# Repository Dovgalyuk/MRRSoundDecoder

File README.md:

# Maple RailRoad Sound Decoder

WiFi controller, sound decoder, and sound projects for model trains.

Project includes library for programming the sounds with set of state machines.

There are several ready-to-use sample sound projects.

# Project structure

* esp32 - firmwares for decoder and command station
* hardware - several versions of PCBs for manufacturing the decoder
* projects - ready-to-use sound projects for different locomotives
* compiler - compiler for the sound projects
* emulator - cab emulator for listening sounds with virtual locomotive control
* sample - dummy player which generates wav file by interpreting the sound project
* other directories include the source code of the firmware

# Bringing locomotive to life

* Get the hardware (order PCB, solder the components)
* Build firmware
  * Install ESP32 toolkit (esp idf)
  * Run esp32/decoder/build32M.sh (or other version)
* Upload esp32/decoder/build32M/esp32sounddecoder.bin into the ESP32 module
* Build selected sound project with compiler/compiler.py
* Upload built project through the web interface into the controller
* Install the controller into the locomotive

# Software features

Controller provides web interface that may be accessed through
WiFi (default address 192.168.4.1).

Sound module plays 8- or 16-bit sounds in 8 channels.

Output functions and sound schemes are programmed with
custom language. The scripts may include conditions,
loops, and finite state machines. These features
may be used for creating complex sound projects.

# Hardware

Controller is intended to be used with G-scale locomotives
with lithium batteries installed, but it may also be used
with track power (some power capacitors are probably needed).

Controller includes the following hardware components:
* ESP32 CPU with embedded WiFi module and flash memory
* Motor driver
* I2S audio power amplifier (MAX98357A)
* 7 programmable outputs
* BEMF for adjusting the motor speed (work in progress)

# Roadmap

* BEMF with new motor driver
* Support of logical input/outputs
* H0-compatible PCB

# Links

* Radio-controlled engines with sound
  - https://github.com/TheDIYGuy999/Rc_Engine_Sound_ESP32
* Cost effective DIY DCC Decoder for model railroad locomotives
  - https://github.com/gab-k/RP2040-Decoder
* NIMRS: open-source NIMRS-21Pin-Decoder, based on the ESP32-S3 microcontroller
  - https://github.com/CDFER/NIMRS-21Pin-Decoder
  - https://github.com/ProjectInitiative/NIMRS-Firmware

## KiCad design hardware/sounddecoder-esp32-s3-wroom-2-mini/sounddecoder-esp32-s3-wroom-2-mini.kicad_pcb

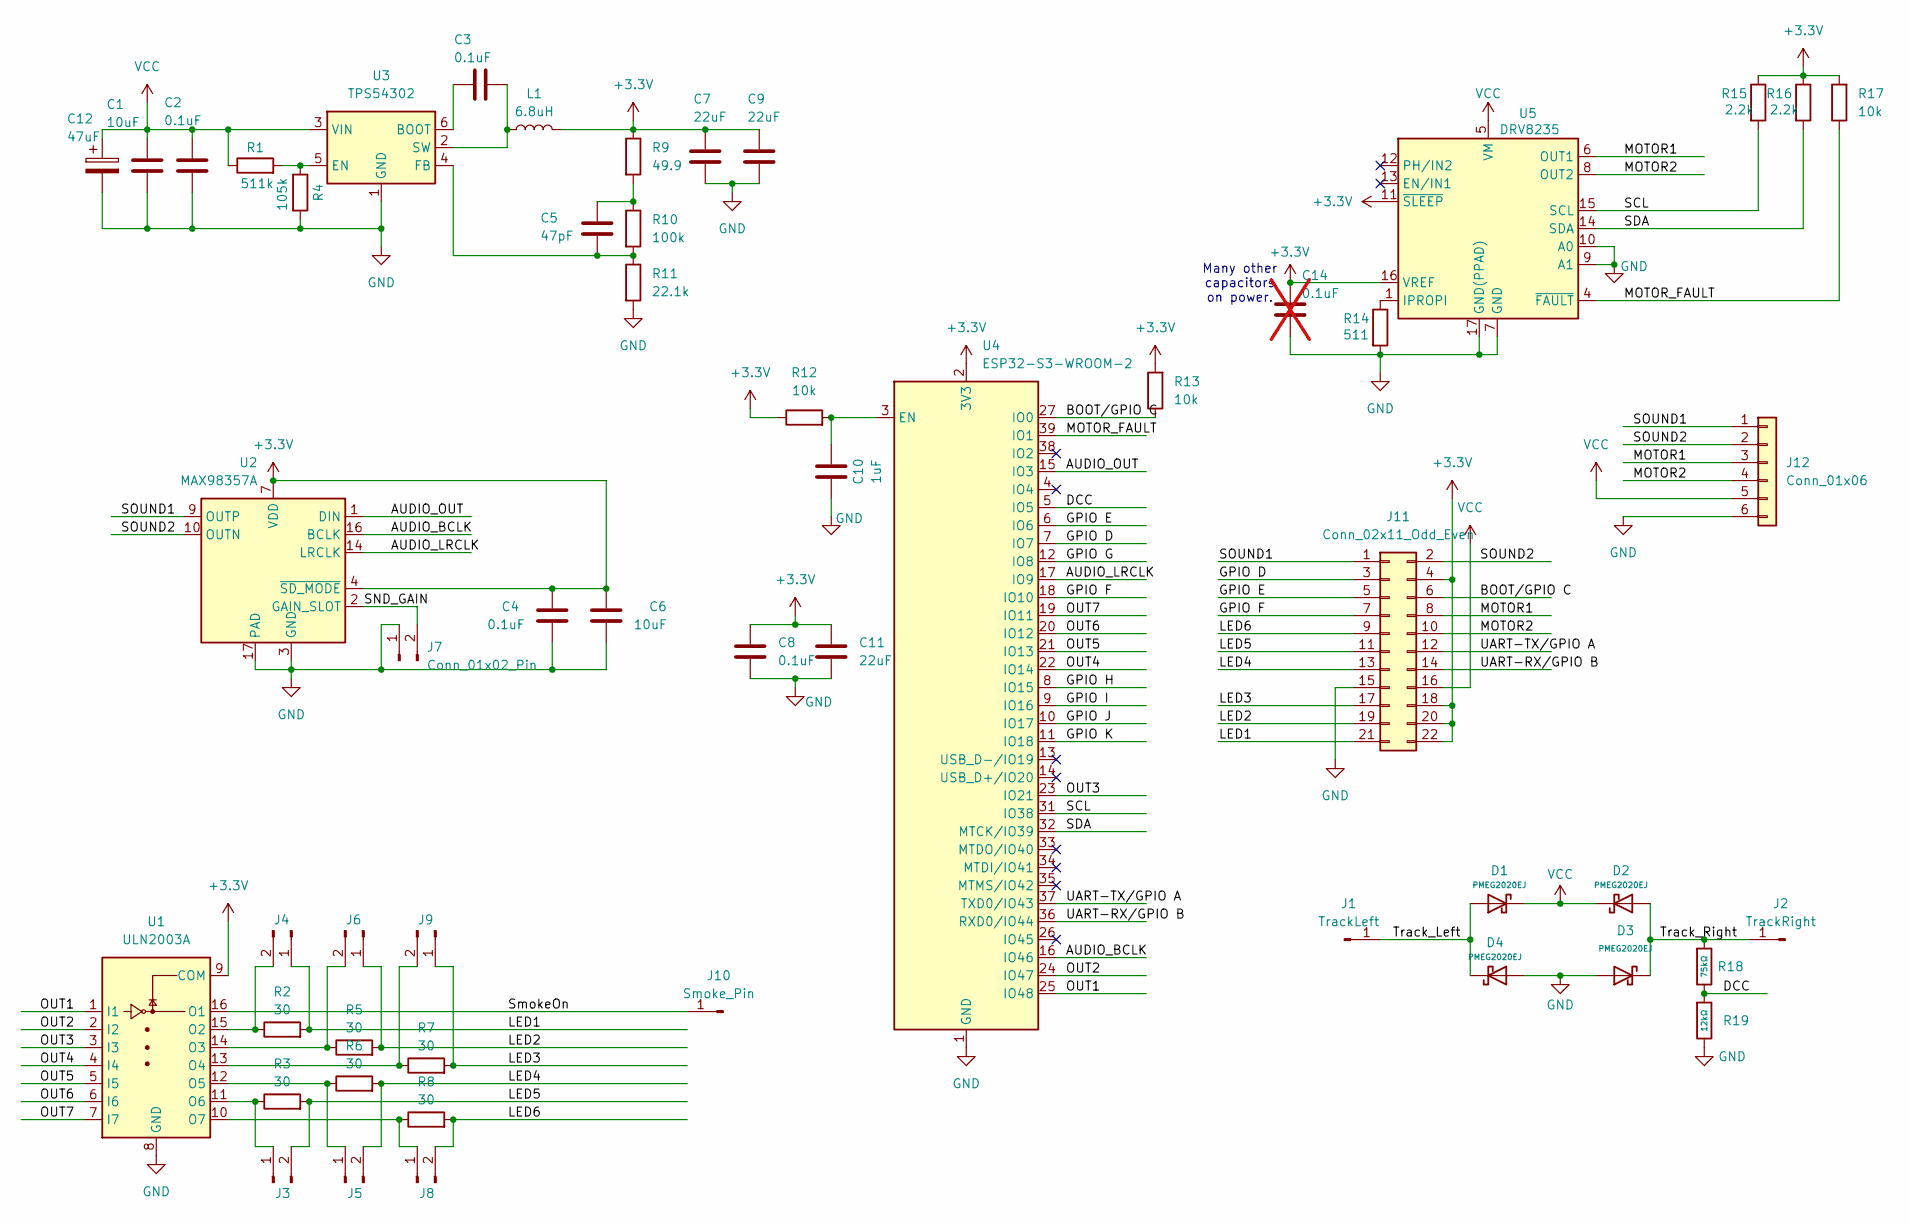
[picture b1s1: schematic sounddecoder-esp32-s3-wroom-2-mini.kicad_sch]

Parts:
C1, C6: 10uF; C_0603_1608Metric
C2, C3, C4, C8: 0.1uF; C_0603_1608Metric
C5: 47pF; C_0603_1608Metric
C7, C9, C11: 22uF; C_0603_1608Metric
C10: 1uF; C_0603_1608Metric
C12: 47uF; CP_Elec_6.3x5.4
C14: 0.1uF; C_0603_1608Metric; not fitted
D1, D2, D3, D4: PMEG2020EJ; D_SOD-323; Forward Voltage (Vf@If) 450mV@1.0A; Reverse Voltage (Vr) 20V; Part B5817WS; LCSC C7420329
J1: TrackLeft; TestPoint_THTPad_1.0x1.0mm_Drill0.5mm
J2: TrackRight; TestPoint_THTPad_1.0x1.0mm_Drill0.5mm
J3, J4, J5, J6, J7, J8, J9: Conn_01x02_Pin; SolderJumper-2_P1.3mm_Open_RoundedPad1.0x1.5mm
J10: Smoke_Pin; TestPoint_THTPad_1.0x1.0mm_Drill0.5mm
J11: Conn_02x11_Odd_Even; PinHeader_2x11_P2.00mm_Vertical
J12: Conn_01x06; PinHeader_1x06_P2.54mm_Vertical
L1: 6.8uH; L_Chilisin_BMRA00050530
R1: 511k; C_0603_1608Metric
R2, R3, R5, R6, R7, R8: 30; C_0603_1608Metric
R4: 105k; C_0603_1608Metric
R9: 49.9; C_0603_1608Metric
R10: 100k; C_0603_1608Metric
R11: 22.1k; C_0603_1608Metric
R12, R13, R17: 10k; C_0603_1608Metric
R14: 511; C_0603_1608Metric
R15, R16: 2.2k; C_0603_1608Metric
R18: 75kΩ; C_0603_1608Metric; Overload Voltage (Max) 50V; Tolerance ±1%; Part 0402WGF7502TCE; LCSC C25798
R19: 12kΩ; C_0603_1608Metric; Overload Voltage (Max) 50V; Tolerance ±1%; Part 0402WGF2002TCE; LCSC C25765
U1: ULN2003A; SO-16_3.9x9.9mm_P1.27mm
U2: MAX98357A; TQFN-16-1EP_3x3mm_P0.5mm_EP1.23x1.23mm
U3: TPS54302; SOT-23-6
U4: ESP32-S3-WROOM-2
U5: DRV8235; WQFN-16-1EP_3x3mm_P0.5mm_EP1.68x1.68mm_ThermalVias

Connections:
+3.3V: C4.1, C6.1, C7.1, C8.1, C9.1, C11.1, C14.1, J11.4, J11.18, J11.20, J11.22, L1.2, R9.1, R12.1, R13.2, R15.1, R16.1, R17.2, U1.9 (COM), U2.4 (~SD_MODE), U2.7 (VDD), U2.8 (VDD), U4.2 (3V3), U5.11 (~SLEEP), U5.16 (VREF)
/AUDIO_BCLK: U2.16 (BCLK), U4.16 (IO46)
/AUDIO_LRCLK: U2.14 (LRCLK), U4.17 (IO9)
/AUDIO_OUT: U2.1 (DIN), U4.15 (IO3)
/BOOT/GPIO C: J11.6, R13.1, U4.27 (IO0)
/DCC: R18.2, R19.1, U4.5 (IO5)
/GPIO D: J11.3, U4.7 (IO7)
/GPIO E: J11.5, U4.6 (IO6)
/GPIO F: J11.7, U4.18 (IO10)
/GPIO G: U4.12 (IO8)
/GPIO H: U4.8 (IO15)
/GPIO I: U4.9 (IO16)
/GPIO J: U4.10 (IO17)
/GPIO K: U4.11 (IO18)
/LED1: J4.1, J11.21, R2.2
/LED2: J6.1, J11.19, R5.2
/LED3: J9.1, J11.17, R7.2
/LED4: J5.2, J11.13, R6.2
/LED5: J3.2, J11.11, R3.2
/LED6: J8.2, J11.9, R8.2
/MOTOR1: J11.8, J12.3, U5.6 (OUT1)
/MOTOR2: J11.10, J12.4, U5.8 (OUT2)
/MOTOR_FAULT: R17.1, U4.39 (IO1), U5.4 (~FAULT)
/OUT1: U1.1 (I1), U4.25 (IO48)
/OUT2: U1.2 (I2), U4.24 (IO47)
/OUT3: U1.3 (I3), U4.23 (IO21)
/OUT4: U1.4 (I4), U4.22 (IO14)
/OUT5: U1.5 (I5), U4.21 (IO13)
/OUT6: U1.6 (I6), U4.20 (IO12)
/OUT7: U1.7 (I7), U4.19 (IO11)
/SCL: R15.2, U4.31 (IO38), U5.15 (SCL)
/SDA: R16.2, U4.32 (MTCK/IO39), U5.14 (SDA)
/SND_GAIN: J7.2, U2.2 (GAIN_SLOT)
/SOUND1: J11.1, J12.1, U2.9 (OUTP)
/SOUND2: J11.2, J12.2, U2.10 (OUTN)
/SmokeOn: J10.1, U1.16 (O1)
/Track_Left: D1.2, D4.1, J1.1
/Track_Right: D2.2, D3.1, J2.1, R18.1
/UART-RX/GPIO B: J11.14, U4.36 (RXD0/IO44)
/UART-TX/GPIO A: J11.12, U4.37 (TXD0/IO43)
GND: C1.2, C2.2, C4.2, C6.2, C7.2, C8.2, C9.2, C10.1, C11.2, C12.2, C14.2, D3.2, D4.2, J7.1, J11.15, J12.6, R4.2, R11.2, R14.2, R19.2, U1.8 (GND), U2.3 (GND), U2.11 (GND), U2.15 (GND), U2.17 (PAD), U3.1 (GND), U4.1 (GND), U4.40 (GND), U4.41 (GND), U5.7 (GND), U5.9 (A1), U5.10 (A0), U5.17 (GND(PPAD))
unnamed: C5.1, R9.2, R10.1
unnamed: J3.1, R3.1, U1.11 (O6)
unnamed: J4.2, R2.1, U1.15 (O2)
unnamed: J5.1, R6.1, U1.12 (O5)
unnamed: J6.2, R5.1, U1.14 (O3)
unnamed: J8.1, R8.1, U1.10 (O7)
unnamed: J9.2, R7.1, U1.13 (O4)
unnamed: C3.1, U3.6 (BOOT)
unnamed: R1.2, R4.1, U3.5 (EN)
unnamed: C5.2, R10.2, R11.1, U3.4 (FB)
unnamed: C3.2, L1.1, U3.2 (SW)
unnamed: C10.2, R12.2, U4.3 (EN)
unnamed: R14.1, U5.1 (IPROPI)
VCC: C1.1, C2.1, C12.1, D1.1, D2.1, J11.16, J12.5, R1.1, U3.3 (VIN), U5.5 (VM)

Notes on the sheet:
Many other capacitors on power.

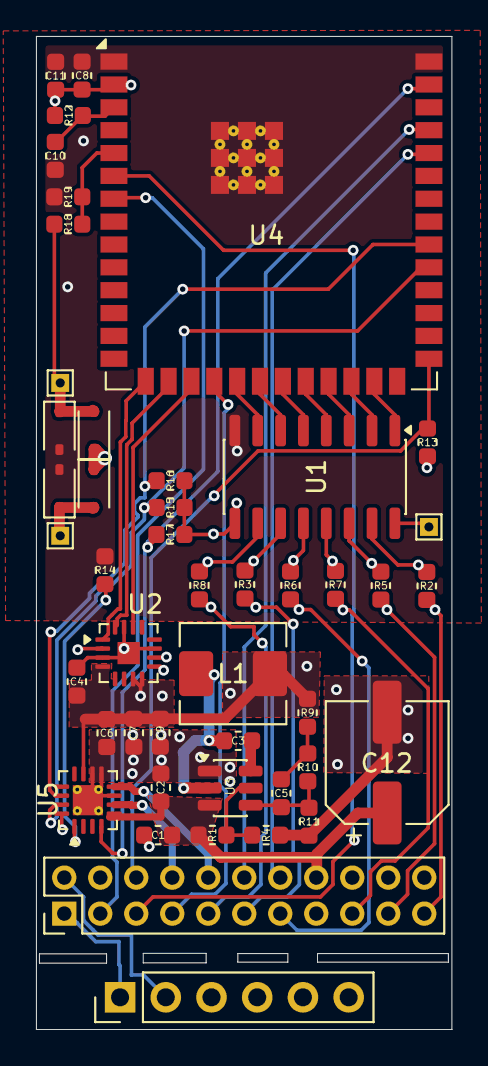
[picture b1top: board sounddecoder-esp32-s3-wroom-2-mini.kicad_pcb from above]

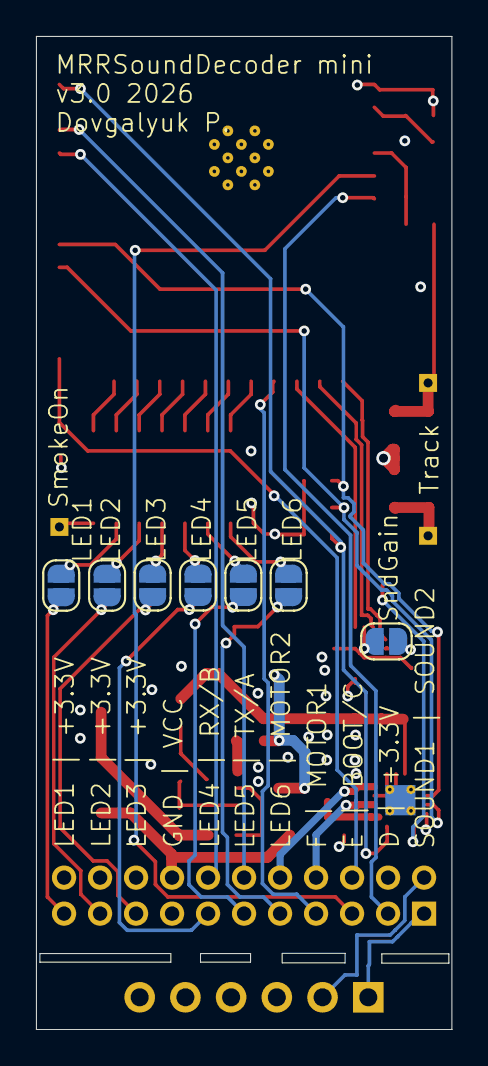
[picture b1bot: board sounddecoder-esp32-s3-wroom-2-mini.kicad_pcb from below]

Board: 4 copper layers, 23.1 x 55.2 mm, 53 parts (7 on the bottom side), 50 nets.

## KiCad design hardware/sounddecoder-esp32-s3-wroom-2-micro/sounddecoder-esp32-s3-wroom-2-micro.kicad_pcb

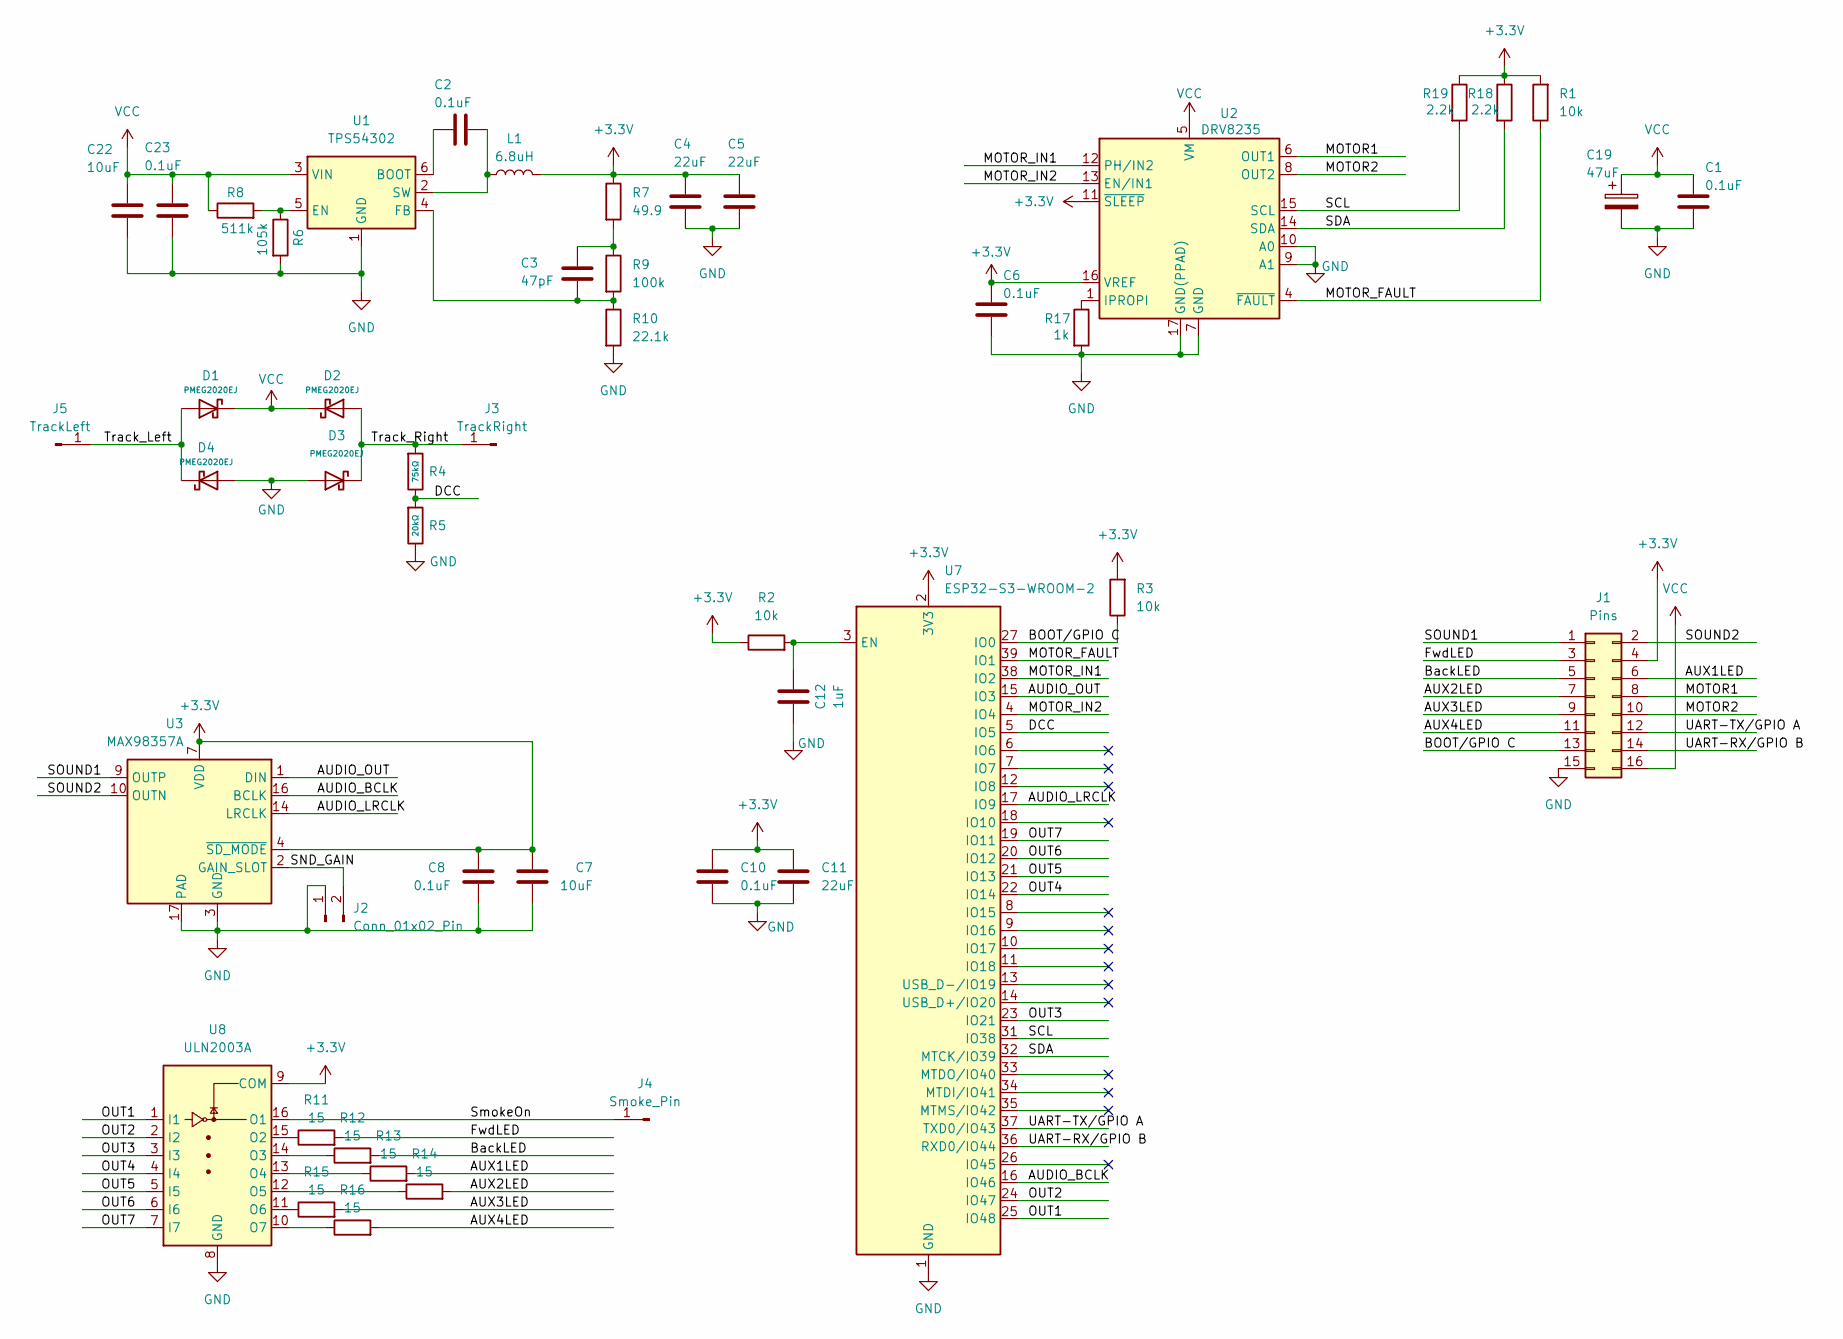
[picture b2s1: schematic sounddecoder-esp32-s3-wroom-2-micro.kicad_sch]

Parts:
C1, C2, C6, C8, C10, C23: 0.1uF; C_0603_1608Metric
C3: 47pF; C_0603_1608Metric
C4, C5, C11: 22uF; C_0603_1608Metric
C7, C22: 10uF; C_0603_1608Metric
C12: 1uF; C_0603_1608Metric
C19: 47uF; CP_Elec_6.3x5.4
D1, D2, D3, D4: PMEG2020EJ; D_SOD-323; Forward Voltage (Vf@If) 450mV@1.0A; Reverse Voltage (Vr) 20V; Part B5817WS; LCSC C7420329
J1: Pins; PinHeader_2x08_P2.00mm_Vertical
J2: Conn_01x02_Pin; SolderJumper-2_P1.3mm_Open_RoundedPad1.0x1.5mm
J3: TrackRight; TestPoint_THTPad_1.0x1.0mm_Drill0.5mm
J4: Smoke_Pin; TestPoint_THTPad_1.0x1.0mm_Drill0.5mm
J5: TrackLeft; TestPoint_THTPad_1.0x1.0mm_Drill0.5mm
L1: 6.8uH; L_Chilisin_BMRA00050530
R1, R2, R3: 10k; C_0603_1608Metric
R4: 75kΩ; C_0603_1608Metric; Overload Voltage (Max) 50V; Tolerance ±1%; Part 0402WGF7502TCE; LCSC C25798
R5: 20kΩ; C_0603_1608Metric; Overload Voltage (Max) 50V; Tolerance ±1%; Part 0402WGF2002TCE; LCSC C25765
R6: 105k; C_0603_1608Metric
R7: 49.9; C_0603_1608Metric
R8: 511k; C_0603_1608Metric
R9: 100k; C_0603_1608Metric
R10: 22.1k; C_0603_1608Metric
R11, R12, R13, R14, R15, R16: 15; C_0603_1608Metric
R17: 1k; C_0603_1608Metric
R18, R19: 2.2k; C_0603_1608Metric
U1: TPS54302; SOT-23-6
U2: DRV8235; WQFN-16-1EP_3x3mm_P0.5mm_EP1.68x1.68mm_ThermalVias
U3: MAX98357A; TQFN-16-1EP_3x3mm_P0.5mm_EP1.23x1.23mm
U7: ESP32-S3-WROOM-2
U8: ULN2003A; SO-16_3.9x9.9mm_P1.27mm

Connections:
+3.3V: C4.1, C5.1, C6.1, C7.1, C8.1, C10.1, C11.1, J1.4, L1.2, R1.2, R2.1, R3.2, R7.1, R18.1, R19.1, U2.11 (~SLEEP), U2.16 (VREF), U3.4 (~SD_MODE), U3.7 (VDD), U3.8 (VDD), U7.2 (3V3), U8.9 (COM)
/AUDIO_BCLK: U3.16 (BCLK), U7.16 (IO46)
/AUDIO_LRCLK: U3.14 (LRCLK), U7.17 (IO9)
/AUDIO_OUT: U3.1 (DIN), U7.15 (IO3)
/AUX1LED: J1.6, R13.2
/AUX2LED: J1.7, R14.2
/AUX3LED: J1.9, R15.2
/AUX4LED: J1.11, R16.2
/BOOT/GPIO C: J1.13, R3.1, U7.27 (IO0)
/BackLED: J1.5, R12.2
/DCC: R4.2, R5.1, U7.5 (IO5)
/FwdLED: J1.3, R11.2
/MOTOR1: J1.8, U2.6 (OUT1)
/MOTOR2: J1.10, U2.8 (OUT2)
/MOTOR_FAULT: R1.1, U2.4 (~FAULT), U7.39 (IO1)
/MOTOR_IN1: U2.12 (PH/IN2), U7.38 (IO2)
/MOTOR_IN2: U2.13 (EN/IN1), U7.4 (IO4)
/OUT1: U7.25 (IO48), U8.1 (I1)
/OUT2: U7.24 (IO47), U8.2 (I2)
/OUT3: U7.23 (IO21), U8.3 (I3)
/OUT4: U7.22 (IO14), U8.4 (I4)
/OUT5: U7.21 (IO13), U8.5 (I5)
/OUT6: U7.20 (IO12), U8.6 (I6)
/OUT7: U7.19 (IO11), U8.7 (I7)
/SCL: R19.2, U2.15 (SCL), U7.31 (IO38)
/SDA: R18.2, U2.14 (SDA), U7.32 (MTCK/IO39)
/SND_GAIN: J2.2, U3.2 (GAIN_SLOT)
/SOUND1: J1.1, U3.9 (OUTP)
/SOUND2: J1.2, U3.10 (OUTN)
/SmokeOn: J4.1, U8.16 (O1)
/Track_Left: D1.2, D4.1, J5.1
/Track_Right: D2.2, D3.1, J3.1, R4.1
/UART-RX/GPIO B: J1.14, U7.36 (RXD0/IO44)
/UART-TX/GPIO A: J1.12, U7.37 (TXD0/IO43)
GND: C1.2, C4.2, C5.2, C6.2, C7.2, C8.2, C10.2, C11.2, C12.1, C19.2, C22.2, C23.2, D3.2, D4.2, J1.15, J2.1, R5.2, R6.2, R10.2, R17.2, U1.1 (GND), U2.7 (GND), U2.9 (A1), U2.10 (A0), U2.17 (GND(PPAD)), U3.3 (GND), U3.11 (GND), U3.15 (GND), U3.17 (PAD), U7.1 (GND), U7.40 (GND), U7.41 (GND), U8.8 (GND)
unnamed: C3.1, R7.2, R9.1
unnamed: C2.1, U1.6 (BOOT)
unnamed: R6.1, R8.2, U1.5 (EN)
unnamed: C3.2, R9.2, R10.1, U1.4 (FB)
unnamed: C2.2, L1.1, U1.2 (SW)
unnamed: R17.1, U2.1 (IPROPI)
unnamed: C12.2, R2.2, U7.3 (EN)
unnamed: R11.1, U8.15 (O2)
unnamed: R12.1, U8.14 (O3)
unnamed: R13.1, U8.13 (O4)
unnamed: R14.1, U8.12 (O5)
unnamed: R15.1, U8.11 (O6)
unnamed: R16.1, U8.10 (O7)
VCC: C1.1, C19.1, C22.1, C23.1, D1.1, D2.1, J1.16, R8.1, U1.3 (VIN), U2.5 (VM)

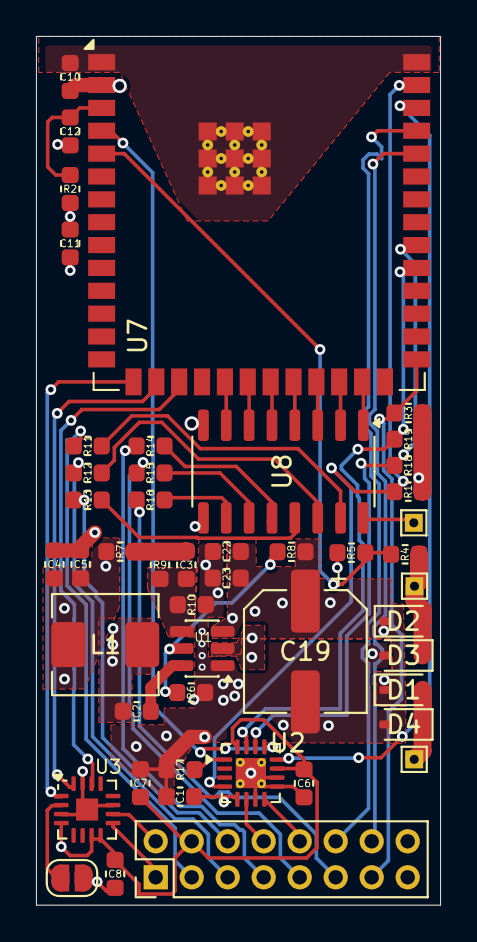
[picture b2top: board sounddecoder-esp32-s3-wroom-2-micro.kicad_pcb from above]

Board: 4 copper layers, 22.5 x 48.3 mm, 48 parts (0 on the bottom side), 49 nets.

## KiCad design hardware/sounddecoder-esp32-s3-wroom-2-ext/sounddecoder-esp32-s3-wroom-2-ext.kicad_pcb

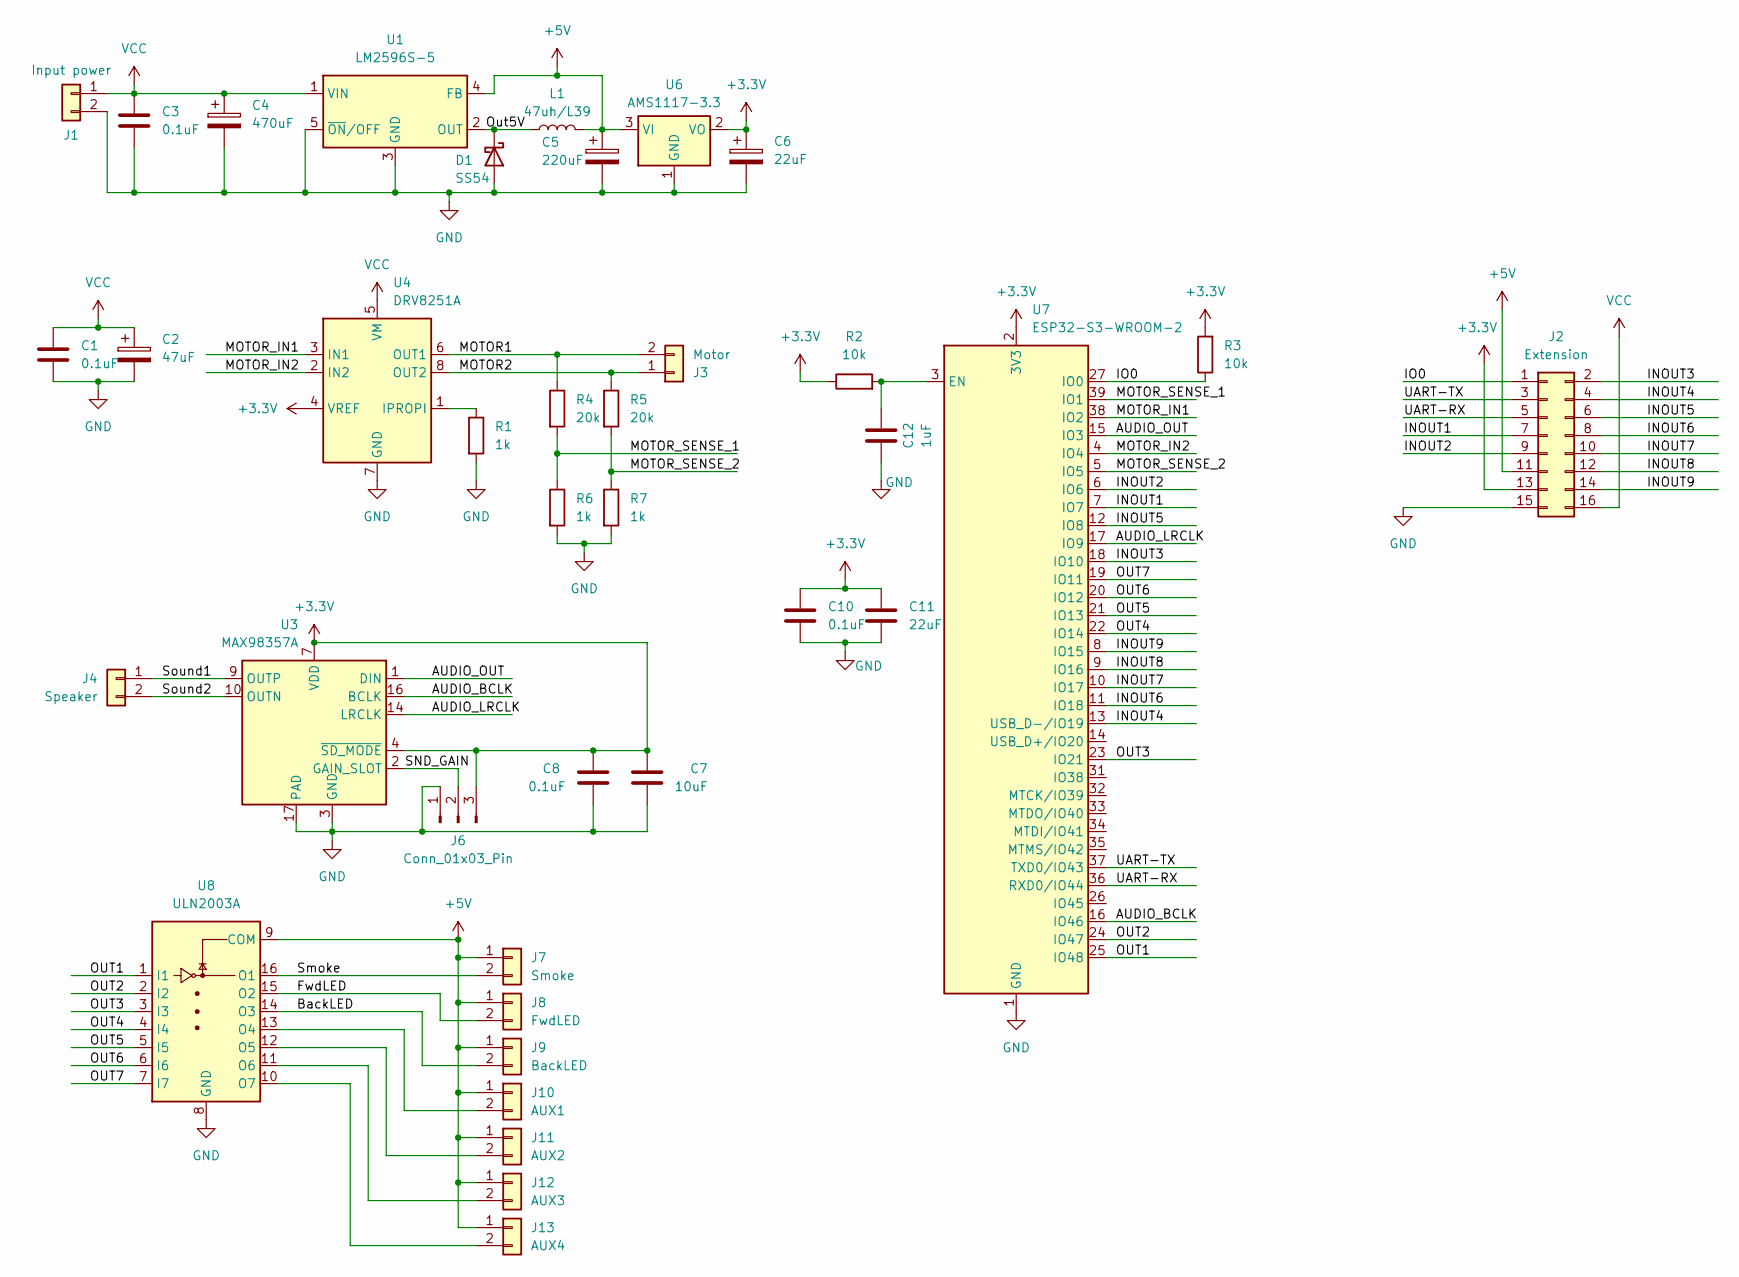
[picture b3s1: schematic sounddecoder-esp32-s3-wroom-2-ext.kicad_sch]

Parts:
C1, C3, C8, C10: 0.1uF; C_0805_2012Metric_Pad1.18x1.45mm_HandSolder
C2: 47uF; CP_Elec_6.3x5.4
C4: 470uF; CP_Elec_10x10.5
C5: 220uF; C_Elec_6.3x7.7
C6: 22uF; CP_Elec_4x5.4
C7: 10uF; C_0805_2012Metric_Pad1.18x1.45mm_HandSolder
C11: 22uF; C_0805_2012Metric_Pad1.18x1.45mm_HandSolder
C12: 1uF; C_0805_2012Metric_Pad1.18x1.45mm_HandSolder
D1: SS54; D_SMC
J1: Input power; TerminalBlock_Xinya_XY308-2.54-2P_1x02_P2.54mm_Horizontal
J2: Extension; PinHeader_2x08_P1.27mm_Vertical_SMD
J3: Motor; TerminalBlock_Xinya_XY308-2.54-2P_1x02_P2.54mm_Horizontal
J4: Speaker; TerminalBlock_Xinya_XY308-2.54-2P_1x02_P2.54mm_Horizontal
J6: Conn_01x03_Pin; PinHeader_1x03_P1.00mm_Vertical
J7: Smoke; TerminalBlock_Xinya_XY308-2.54-2P_1x02_P2.54mm_Horizontal
J8: FwdLED; TerminalBlock_Xinya_XY308-2.54-2P_1x02_P2.54mm_Horizontal
J9: BackLED; TerminalBlock_Xinya_XY308-2.54-2P_1x02_P2.54mm_Horizontal
J10: AUX1; TerminalBlock_Xinya_XY308-2.54-2P_1x02_P2.54mm_Horizontal
J11: AUX2; TerminalBlock_Xinya_XY308-2.54-2P_1x02_P2.54mm_Horizontal
J12: AUX3; TerminalBlock_Xinya_XY308-2.54-2P_1x02_P2.54mm_Horizontal
J13: AUX4; TerminalBlock_Xinya_XY308-2.54-2P_1x02_P2.54mm_Horizontal
L1: 47uh/L39; L_Bourns_SRP1245A
R1, R6, R7: 1k; R_0805_2012Metric_Pad1.20x1.40mm_HandSolder
R2, R3: 10k; R_0805_2012Metric_Pad1.20x1.40mm_HandSolder
R4, R5: 20k; R_0805_2012Metric_Pad1.20x1.40mm_HandSolder
U1: LM2596S-5; TO-263-5_TabPin3
U3: MAX98357A; TQFN-16-1EP_3x3mm_P0.5mm_EP1.23x1.23mm
U4: DRV8251A; Texas_HSOP-8-1EP_3.9x4.9mm_P1.27mm_ThermalVias
U6: AMS1117-3.3; SOT-223-3_TabPin2
U7: ESP32-S3-WROOM-2
U8: ULN2003A; SO-16_3.9x9.9mm_P1.27mm

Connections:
+3.3V: C6.1, C7.1, C8.1, C10.1, C11.1, J2.13, J6.3, R2.1, R3.2, U3.4 (~SD_MODE), U3.7 (VDD), U3.8 (VDD), U4.4 (VREF), U6.2 (VO), U7.2 (3V3)
+5V: C5.1, J2.11, J7.1, J8.1, J9.1, J10.1, J11.1, J12.1, J13.1, L1.2, U1.4 (FB), U6.3 (VI), U8.9 (COM)
/AUDIO_BCLK: U3.16 (BCLK), U7.16 (IO46)
/AUDIO_LRCLK: U3.14 (LRCLK), U7.17 (IO9)
/AUDIO_OUT: U3.1 (DIN), U7.15 (IO3)
/BackLED: J9.2, U8.14 (O3)
/FwdLED: J8.2, U8.15 (O2)
/INOUT1: J2.7, U7.7 (IO7)
/INOUT2: J2.9, U7.6 (IO6)
/INOUT3: J2.2, U7.18 (IO10)
/INOUT4: J2.4, U7.13 (USB_D-/IO19)
/INOUT5: J2.6, U7.12 (IO8)
/INOUT6: J2.8, U7.11 (IO18)
/INOUT7: J2.10, U7.10 (IO17)
/INOUT8: J2.12, U7.9 (IO16)
/INOUT9: J2.14, U7.8 (IO15)
/IO0: J2.1, R3.1, U7.27 (IO0)
/MOTOR1: J3.2, R4.1, U4.6 (OUT1)
/MOTOR2: J3.1, R5.1, U4.8 (OUT2)
/MOTOR_IN1: U4.3 (IN1), U7.38 (IO2)
/MOTOR_IN2: U4.2 (IN2), U7.4 (IO4)
/MOTOR_SENSE_1: R4.2, R6.1, U7.39 (IO1)
/MOTOR_SENSE_2: R5.2, R7.1, U7.5 (IO5)
/OUT1: U7.25 (IO48), U8.1 (I1)
/OUT2: U7.24 (IO47), U8.2 (I2)
/OUT3: U7.23 (IO21), U8.3 (I3)
/OUT4: U7.22 (IO14), U8.4 (I4)
/OUT5: U7.21 (IO13), U8.5 (I5)
/OUT6: U7.20 (IO12), U8.6 (I6)
/OUT7: U7.19 (IO11), U8.7 (I7)
/Out5V: D1.1 (K), L1.1, U1.2 (OUT)
/SND_GAIN: J6.2, U3.2 (GAIN_SLOT)
/Smoke: J7.2, U8.16 (O1)
/Sound1: J4.1, U3.9 (OUTP)
/Sound2: J4.2, U3.10 (OUTN)
/UART-RX: J2.5, U7.36 (RXD0/IO44)
/UART-TX: J2.3, U7.37 (TXD0/IO43)
GND: C1.2, C2.2, C3.2, C4.2, C5.2, C6.2, C7.2, C8.2, C10.2, C11.2, C12.1, D1.2 (A), J1.2, J2.15, J6.1, R1.2, R6.2, R7.2, U1.3 (GND), U1.5 (~ON/OFF), U3.3 (GND), U3.11 (GND), U3.15 (GND), U3.17 (PAD), U4.7 (GND), U4.9 (GND), U6.1 (GND), U7.1 (GND), U7.40 (GND), U7.41 (GND), U8.8 (GND)
unnamed: J10.2, U8.13 (O4)
unnamed: J11.2, U8.12 (O5)
unnamed: J12.2, U8.11 (O6)
unnamed: J13.2, U8.10 (O7)
unnamed: R1.1, U4.1 (IPROPI)
unnamed: C12.2, R2.2, U7.3 (EN)
VCC: C1.1, C2.1, C3.1, C4.1, J1.1, J2.16, U1.1 (VIN), U4.5 (VM)

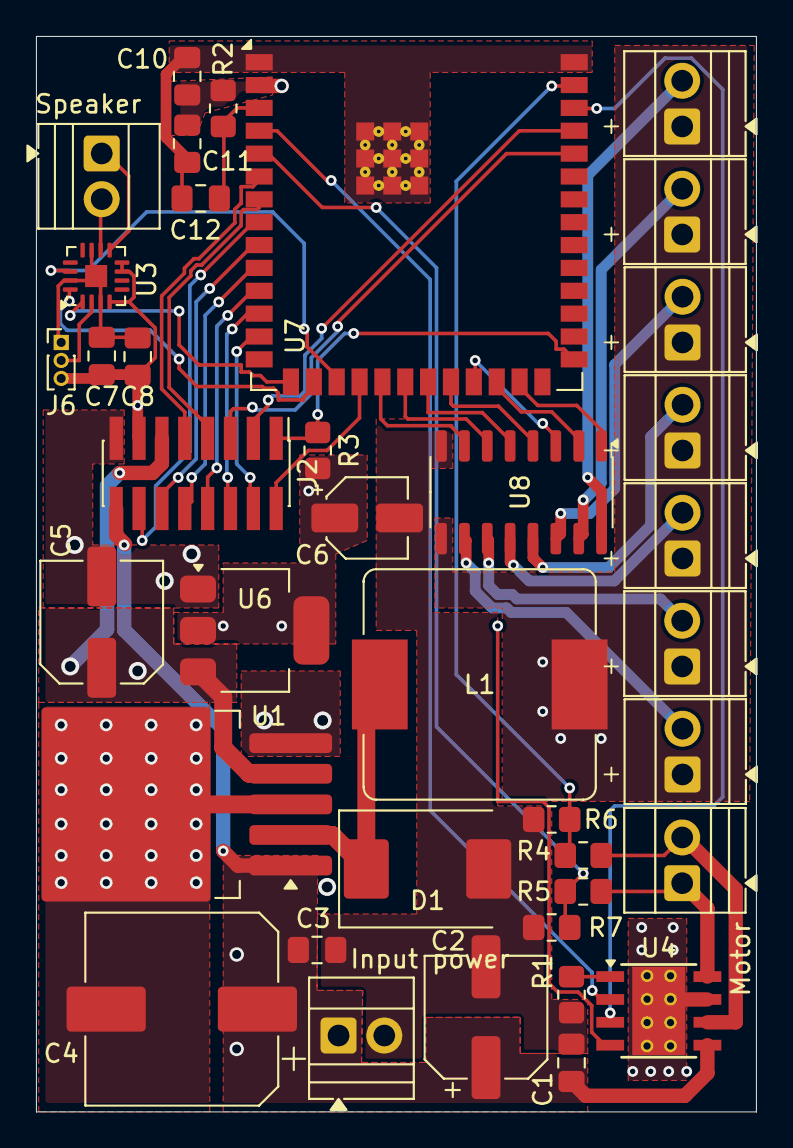
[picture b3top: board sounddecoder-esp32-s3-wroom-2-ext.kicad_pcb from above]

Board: 4 copper layers, 40.0 x 59.8 mm, 38 parts (0 on the bottom side), 45 nets.

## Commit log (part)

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2026-02-25 First version of ESP32 firmware
2026-03-01 Playing prototype
2026-03-05 Improved project structure and web page
2026-03-06 Implemented sound project upload
2026-03-06 Changed SPIFFS to LittleFS
2026-03-07 Decoupled functions and slots
2026-03-08 Added engine control
2026-05-07 First version of compiler
2026-05-08 Added support of new project format
2026-05-21 Many compiler updates.
2026-05-26 Compiler update
2026-05-28 Added 32M config
2026-06-04 Updated schematic
2026-06-30 Many changes
